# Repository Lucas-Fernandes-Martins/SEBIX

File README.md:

# SEBIX

Réplica do Jogo do Dinossauro (Chrome) em um Arduino.

<h2> Descrição </h2>

Jogo do dinossauro da Google feito no Arduino implementado com uma LCD para display e botões para controle no jogo.

<h2> Tecnologias Usadas </h2>

Para o processamento do jogo usamos um Arduino Uno R3. Existe um LCD 16x2 para display do dinossauro e obstáculos do jogo. Três botões para controle do jogo. Um potenciômetro para controle do brilho do Arduino. Um buzzer para emitir sons em certos momentos do jogo. Foi usado a linguagem C++ para programação no Arduino, com a biblioteca Liquid Crystal. O software Eagle foi usado para produção da PCB e o Fusion para a produção de uma caixa para armazenar todos os componentes.

<h2> Esquemático<h2>

<h2> Como Usar </h2>

No menu do jogo é possível acessar uma área de instruções, mas o botão da esquerda sobe o cursor no menu e faz com que o dinossauro pule, o botão do meio abaixa o cursor no menu e faz com que o dinossauro abaixe e o botão da direita confirma a opção no menu e renicia o jogo.

<h2> Imagem da Simulação<h2>

<h2> Membros </h2>

<ul>
  <li>Beatriz Rocha</li>
  <li>David Dias</li>
  <li>Gabriel Rebelo</li>
  <li>Lucas Martins</li>
</ul>

<h2> Agradecimentos </h2>

<ul>
  <li>Érika Cardoso</li>
</ul>

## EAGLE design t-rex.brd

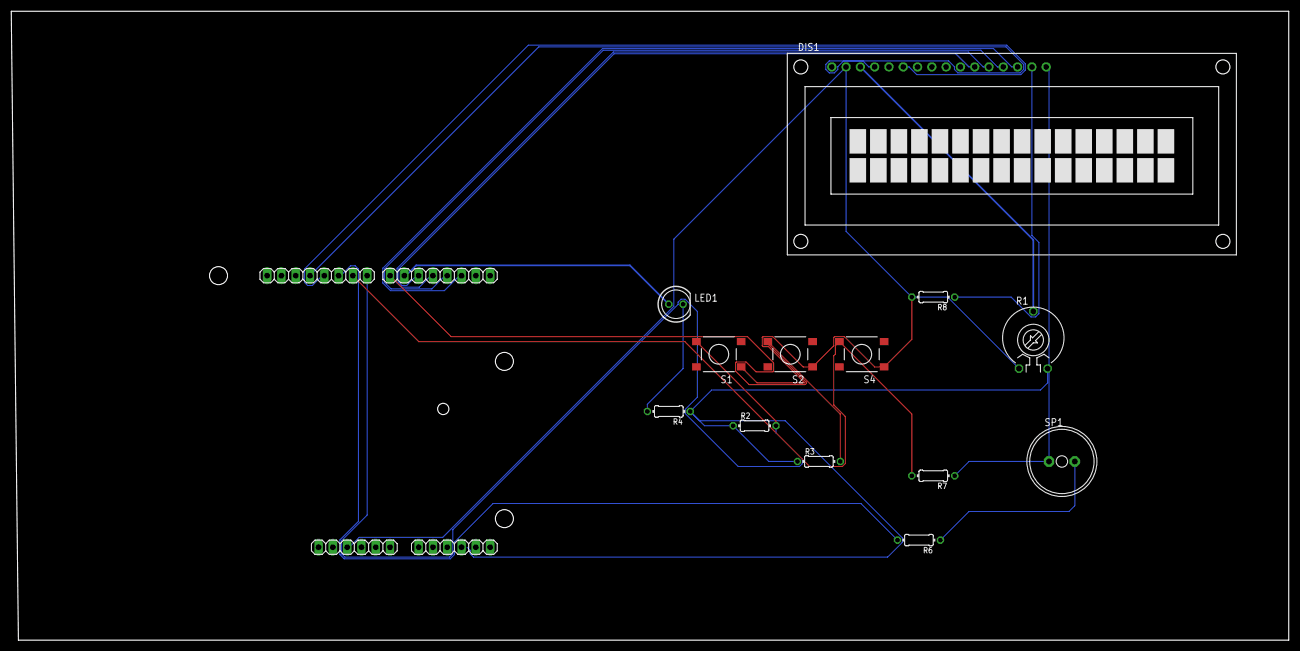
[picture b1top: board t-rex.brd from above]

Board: 2 copper layers, 227.0 x 111.8 mm, 14 parts (0 on the bottom side), 17 nets.

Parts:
DIS1: TUXGR_16X2_R2
IC1: ARDUINO2009
LED1: LED5MM
R1: 10k; PT-10
R2, R3, R7: 100k; 0204/7
R4, R8: 200; 0204/7
R6: 1k; 0204/7
S1, S2, S4: DTSM-6
SP1: AL11P

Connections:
BUT_L: IC1.22, R7.2, S4.4
BUT_M: IC1.21, R2.2, S1.4
BUT_R: IC1.20, R3.2, S2.4
BUZ: IC1.23, R6.2
GND: DIS1.1, DIS1.5, DIS1.16, IC1.4, IC1.5, IC1.27, R1.E, R2.1, R3.1, R4.1, R7.1, SP1.-
unnamed: DIS1.14, IC1.15
unnamed: DIS1.13, IC1.16
unnamed: DIS1.12, IC1.17
unnamed: IC1.19, LED1.A
unnamed: DIS1.11, IC1.18
unnamed: LED1.K, R4.2
unnamed: R6.1, SP1.+
unnamed: DIS1.15, R8.1
PIN11: DIS1.6, IC1.24
PIN12: DIS1.4, IC1.25
POT: DIS1.3, R1.S
POW: DIS1.2, IC1.3, R1.A, R8.2, S1.1, S2.1, S4.1

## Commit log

2021-02-04 Add files via upload
    - Adicionados pulo e animação do dinossauro.
2021-02-04 Rename sebix..ino.txt to sebix..ino
2021-02-04 Rename sebix..ino to sebix.ino
2021-02-19 Rename sebix.ino to lucas.ino
2021-02-19 Meu dinossauro que pula e abaixa mais um menu meio bugado
2021-02-19 Add files via upload
    Código que faz o ptero funcionar. Ainda precisa de polimento.
2021-02-19 Add files via upload
    Geração e movimento dos cactos.
2021-03-05 Esquematico Alt
    Upload no git pra a Érika dar uma olhada e ver se tem algo de errado
2021-03-05 Prototipo de PCB
    Fiz essa pcb ignorando a estranheza de as coisas estarem se conectando diferentemente de como eu imaginava E IMPORTANTE: TINHA UM ERRO NO ESQUEMÁTICO. ONDE ESTÁ CONECTANDO AO PINO 11 NO LCD ERA PRA S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
2021-03-12 corrige erro que cacto e ptero aparecem dps do restart
    corrige o erro em que eles aparecem atrás do player quando ele morre e reinicia o jogo
2021-03-31 Apesar de ta old, essa é a versão mais nova kkkk
2021-04-01 Versão mais nova do codigo
2021-06-04 Versão mais recente
    Corrigido bug de cacto que aparece em cima do player e código beautificado
2021-06-07 Remanejando arquivos
